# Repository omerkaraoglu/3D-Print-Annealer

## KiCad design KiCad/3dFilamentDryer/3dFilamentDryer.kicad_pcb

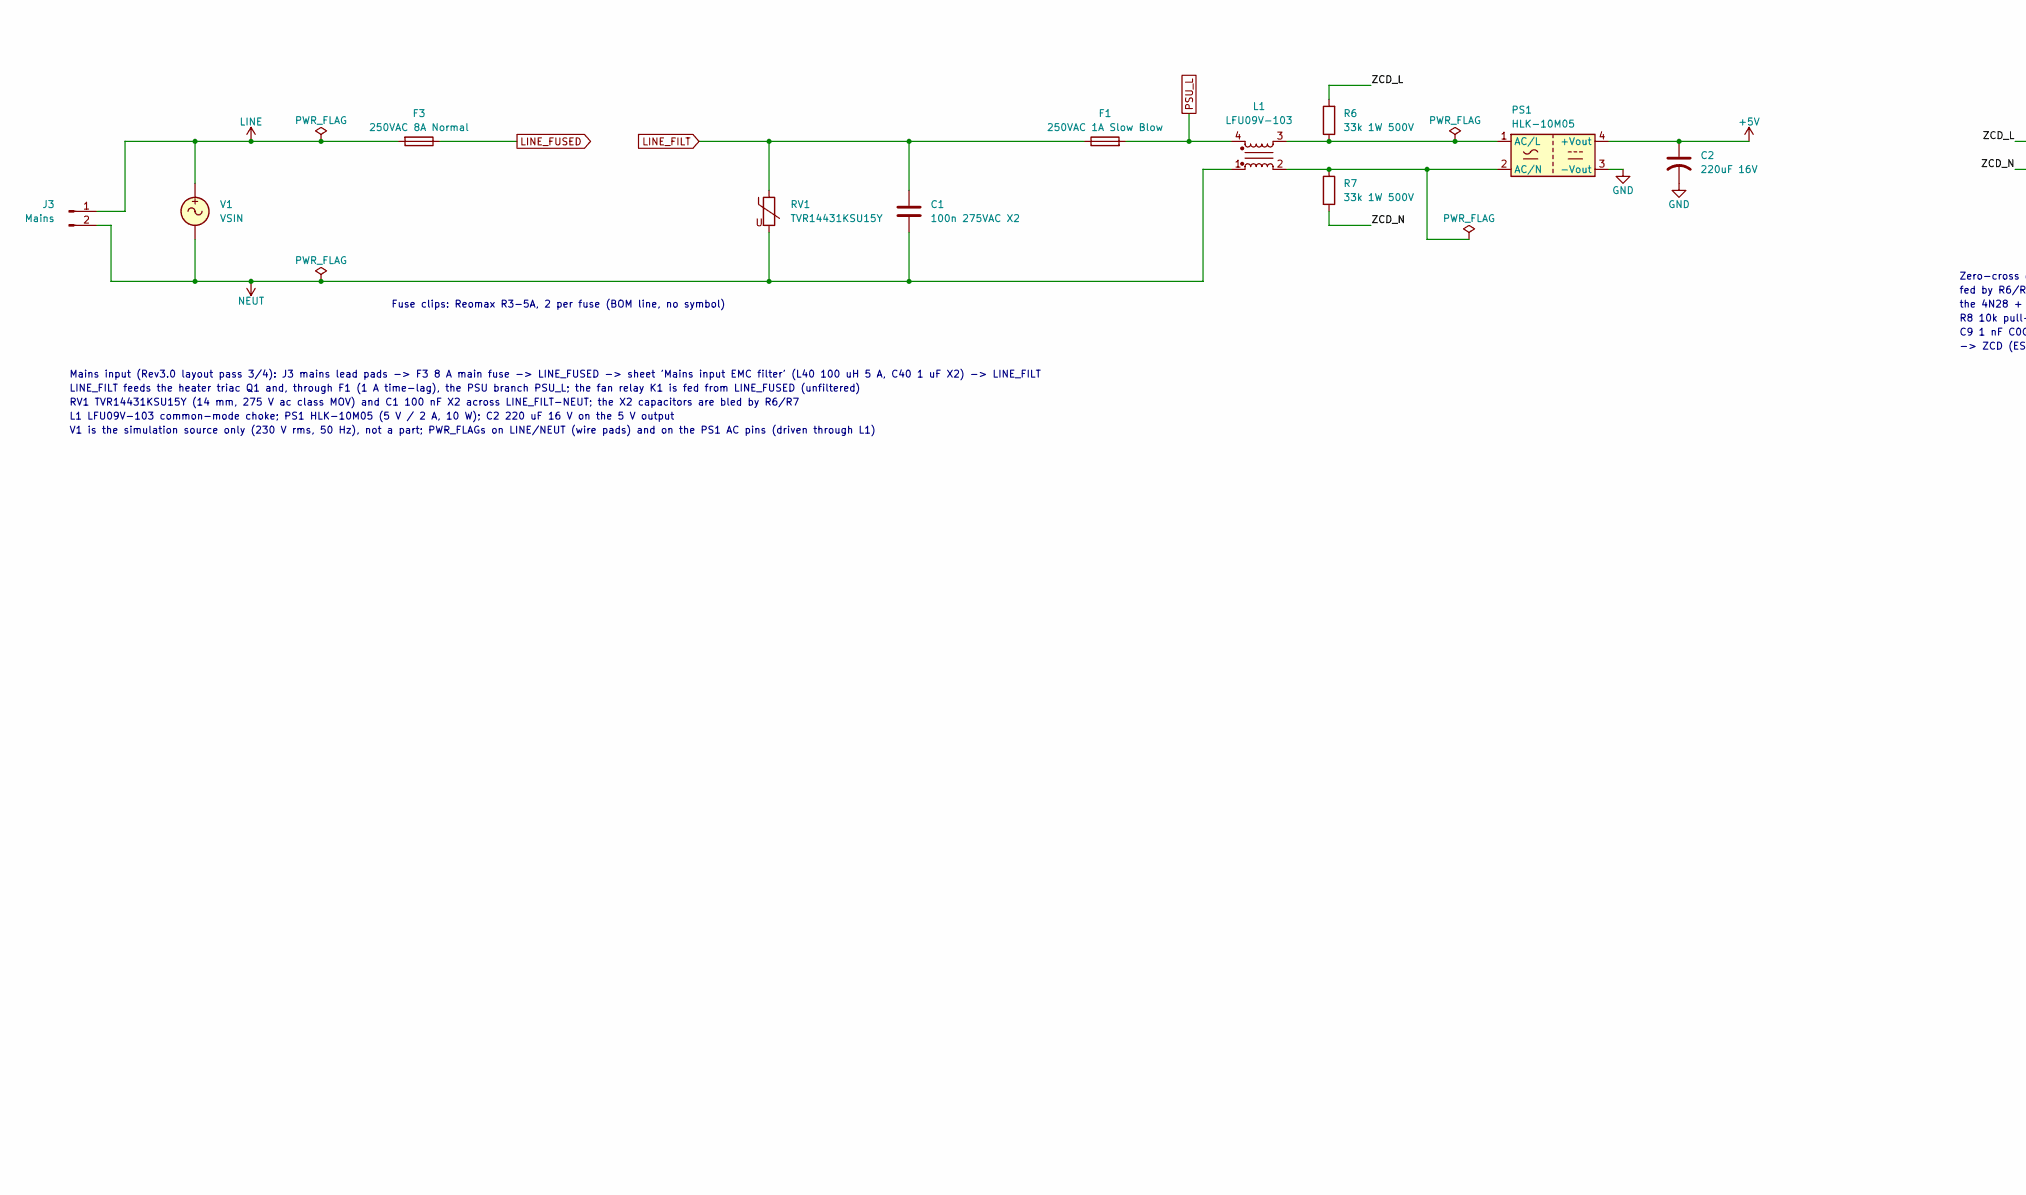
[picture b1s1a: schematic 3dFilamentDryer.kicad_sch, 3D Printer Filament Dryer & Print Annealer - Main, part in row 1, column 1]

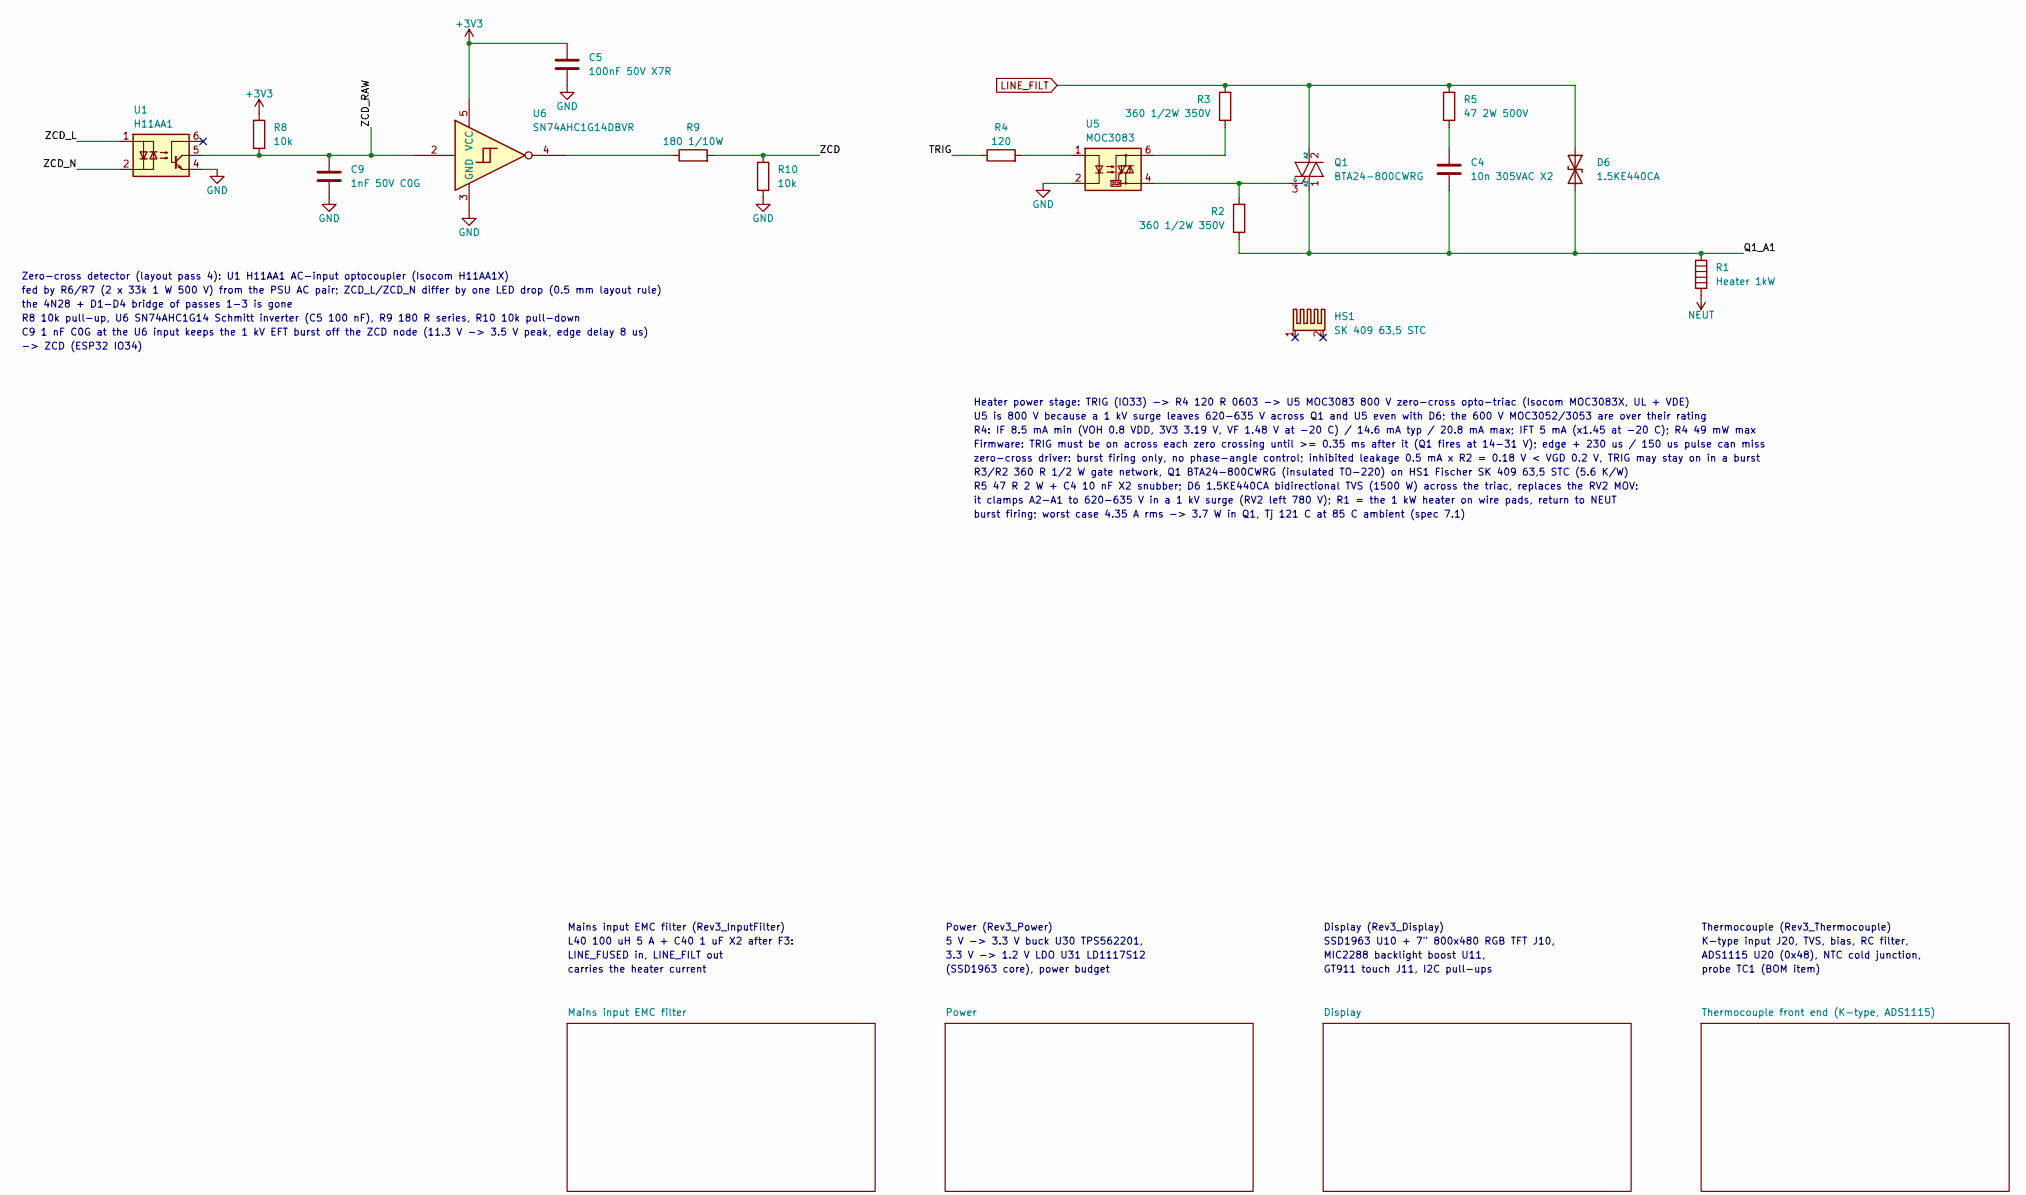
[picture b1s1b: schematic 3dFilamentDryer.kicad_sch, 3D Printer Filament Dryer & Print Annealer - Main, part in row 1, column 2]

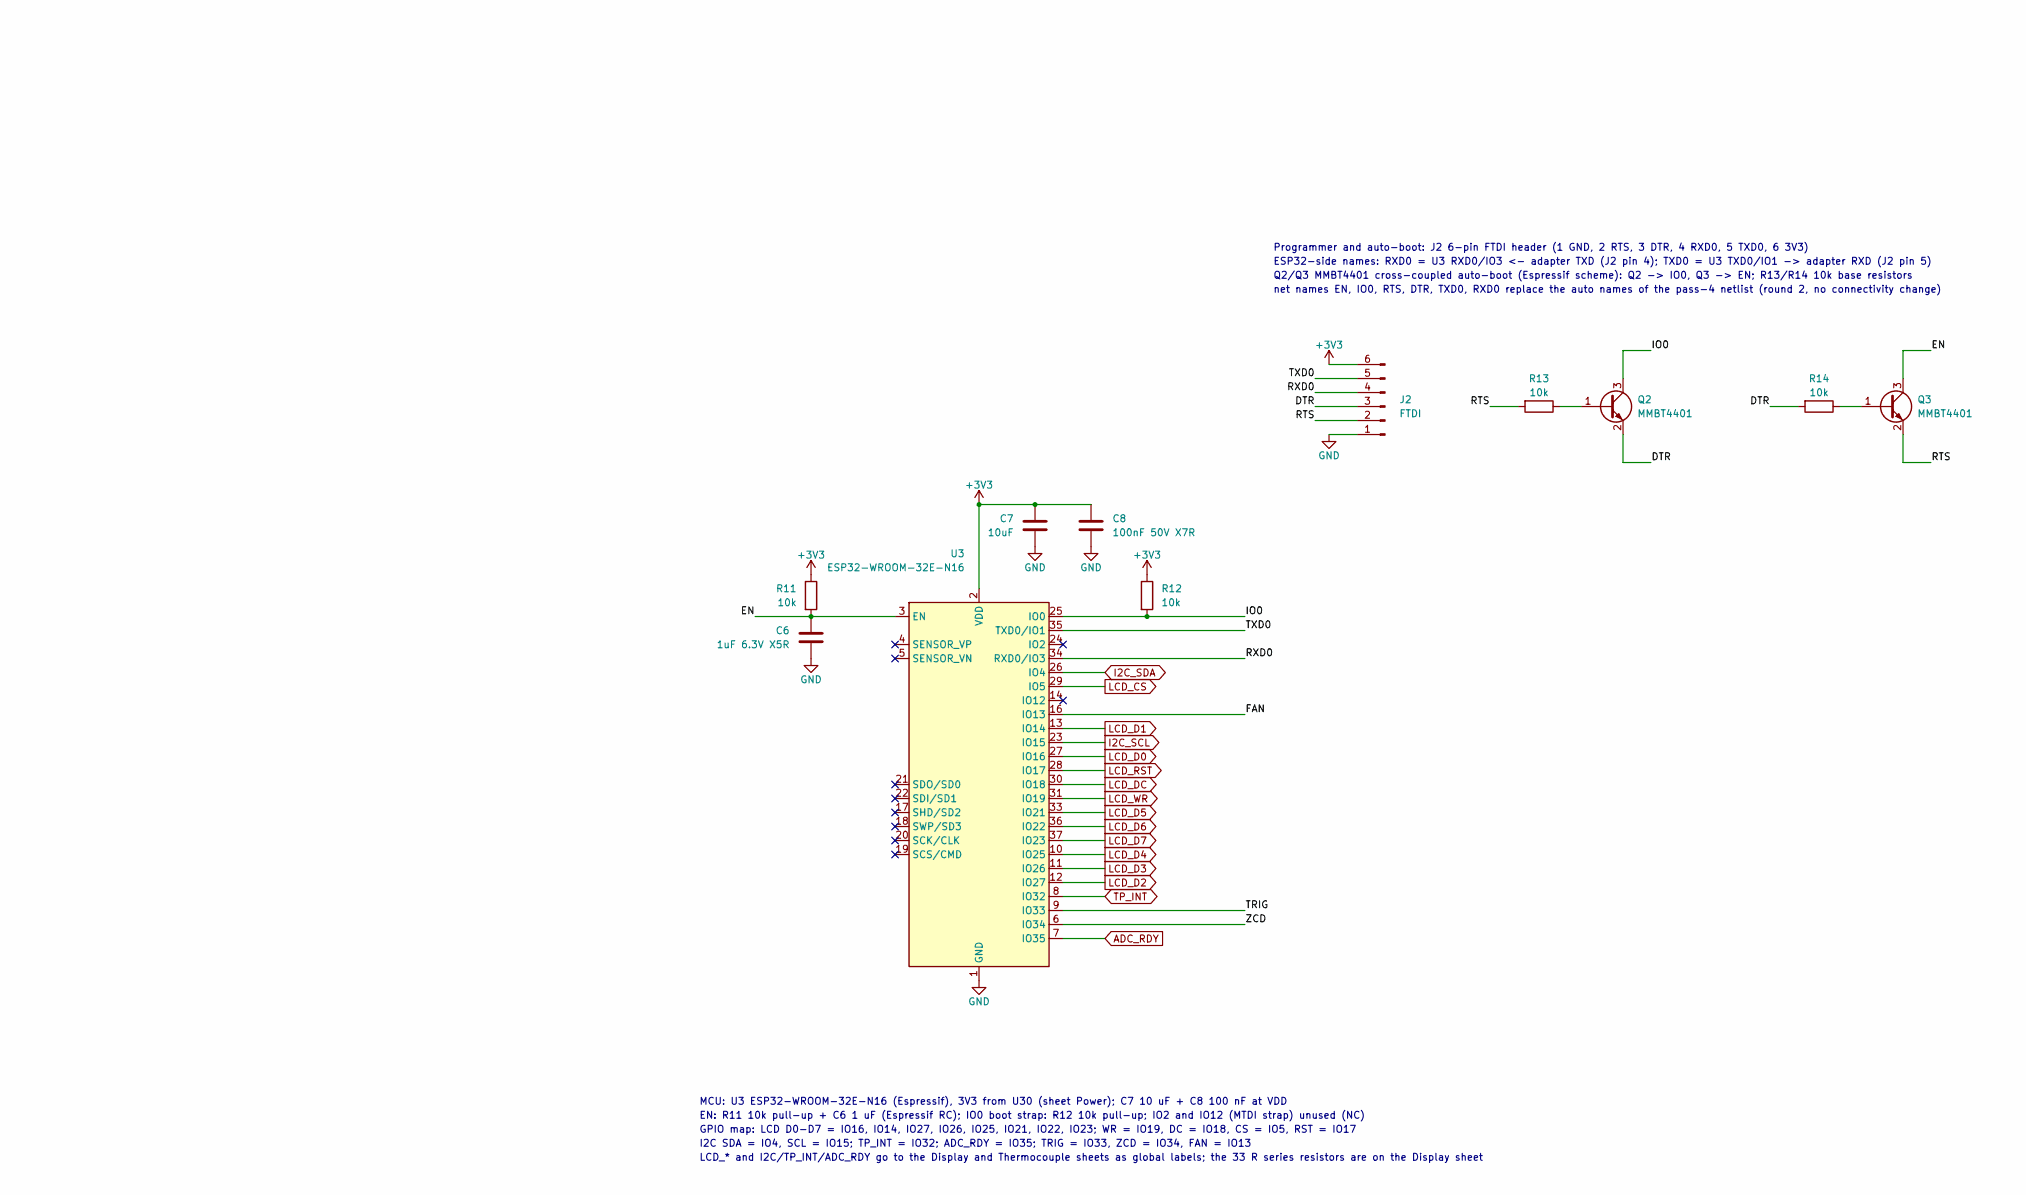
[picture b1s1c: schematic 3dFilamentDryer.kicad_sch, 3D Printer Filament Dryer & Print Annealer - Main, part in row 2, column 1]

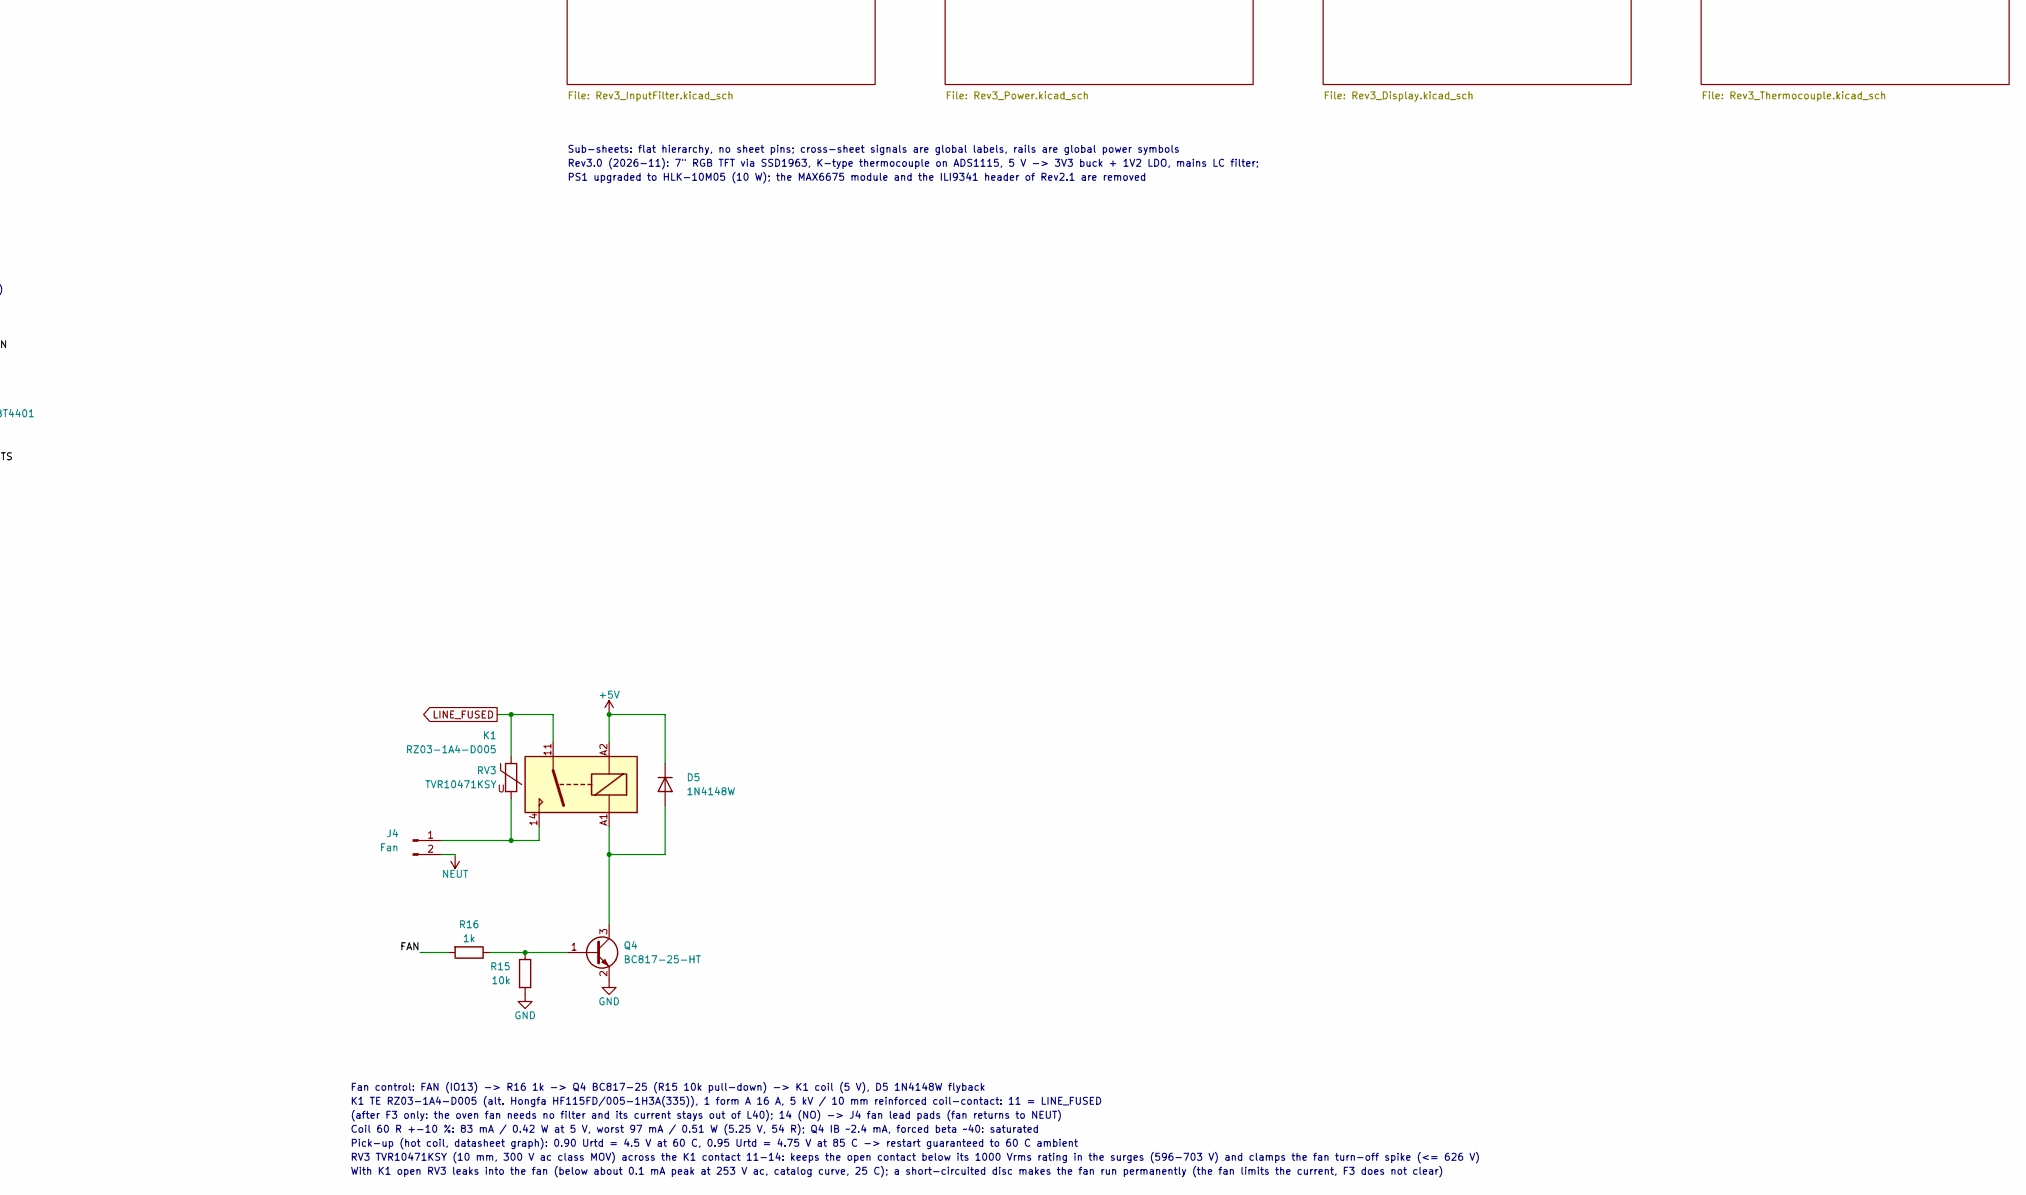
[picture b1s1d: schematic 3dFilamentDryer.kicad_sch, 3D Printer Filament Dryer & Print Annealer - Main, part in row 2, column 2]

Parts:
C1: 100n 275VAC X2; C_Rect_L18.0mm_W5.0mm_P15.00mm_FKS3_FKP3; MPN C42P2104M6SC361
C2: 220uF 16V; C_Radial_D6.3mm_H11.0mm_P2.50mm; MPN PKRJ-016V221ME070-T2.5
C4: 10n 305VAC X2; C_Rect_L13.0mm_W4.0mm_P10.00mm_FKS3_FKP3_MKS4; MPN C42Q2103K40A405
C5, C8: 100nF 50V X7R; C_0402_1005Metric; MPN CC0402KRX7R9BB104
C6: 1uF 6.3V X5R; C_0402_1005Metric; MPN CL05A105KQ5NNNC
C7: 10uF; C_0603_1608Metric; MPN CL10A106KP8NNNC
C9: 1nF 50V C0G; C_0402_1005Metric; MPN CL05C102JB5NNNC
D5: 1N4148W; D_SOD-123; MPN 1N4148W_R1_00301
D6: 1.5KE440CA; D_DO-201AD_P15.24mm_Horizontal; MPN 1.5KE440CA-TKS
F1: 250VAC 1A Slow Blow; Fuseholder_Clip-5x20mm_Littelfuse_445-030_Inline_P20.50x5.2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; MPN STC1A250V
F3: 250VAC 8A Normal; Fuseholder_Clip-5x20mm_Littelfuse_445-030_Inline_P20.50x5.2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; MPN 5GT8A
HS1: SK 409 63,5 STC; Heatsink_Fischer_SK409_63.5_STC; MPN SK 409 63,5 STC TO 220
J2: FTDI; PinHeader_1x06_P2.54mm_Vertical; MPN DS1021-1X6SF11-B
J3: Mains; SolderWire-1.5sqmm_1x02_P7.8mm_D1.7mm_OD3.9mm
J4: Fan; SolderWire-0.75sqmm_1x02_P7mm_D1.25mm_OD3.5mm
K1: RZ03-1A4-D005; Relay_SPST_Schrack-RT1-16A-FormA_RM5mm; MPN RZ03-1A4-D005
L1: LFU09V-103; MPN LFU09V-103
PS1: HLK-10M05; Converter_ACDC_Hi-Link_HLK-10Mxx; MPN HLK-10M05
Q1: BTA24-800CWRG; TO-220-3_Vertical; MPN BTA24-800CWRG
Q2, Q3: MMBT4401; SOT-23-3; MPN MMBT4401-TP
Q4: BC817-25-HT; SOT-23; MPN BC817-25-HT
R1: Heater 1kW; SolderWire-1.5sqmm_1x02_P7.8mm_D1.7mm_OD3.9mm
R2, R3: 360 1/2W 350V; R_Axial_DIN0309_L9.0mm_D3.2mm_P12.70mm_Horizontal; MPN MFR-50FTF52-360R
R4: 120; R_0603_1608Metric; MPN 0603SAJ0121T5E
R5: 47 2W 500V; R_Axial_DIN0414_L11.9mm_D4.5mm_P15.24mm_Horizontal; MPN KNP02SJ0470A10
R6, R7: 33k 1W 500V; R_Axial_DIN0414_L11.9mm_D4.5mm_P5.08mm_Vertical; MPN CFR01SJ0333A10
R8, R10, R11, R12, R13, R14, R15: 10k; R_0402_1005Metric; MPN 0402WGJ0103TCE
R9: 180 1/10W; R_0603_1608Metric; MPN 0603SAJ0181T5E
R16: 1k; R_0402_1005Metric; MPN 0402WGJ0102TCE
RV1: TVR14431KSU15Y; RV_Disc_D15.5mm_W5mm_P7.5mm; MPN TVR14431KSU15Y
RV3: TVR10471KSY; RV_Disc_D12mm_W5.8mm_P7.5mm; MPN TVR10471KSY
U1: H11AA1; DIP-6_W7.62mm; MPN H11AA1X
U3: ESP32-WROOM-32E-N16; ESP32-WROOM-32E; MPN ESP32-WROOM-32E-N16
U5: MOC3083; DIP-6_W7.62mm; MPN MOC3083X
U6: SN74AHC1G14DBVR; SOT-23-5; MPN SN74AHC1G14DBVR
V1: VSIN

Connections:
+3V3: C5.1, C7.1, C8.2, J2.6, R8.1, R11.1, R12.1, U3.2 (VDD), U6.5 (VCC); also elsewhere on the board
+5V: C2.1, D5.1 (K), K1.A2, PS1.4 (+Vout); also elsewhere on the board
/DTR: J2.3, Q2.2 (E), R14.2
/EN: C6.2, Q3.3 (C), R11.2, U3.3 (EN)
/FAN: R16.2, U3.16 (IO13)
/IO0: Q2.3 (C), R12.2, U3.25 (IO0)
/Q1_A1: C4.2, D6.2 (A2), Q1.1 (A1), R1.1, R2.1
/RTS: J2.2, Q3.2 (E), R13.2
/RXD0: J2.4, U3.34 (RXD0/IO3)
/TRIG: R4.1, U3.9 (IO33)
/TXD0: J2.5, U3.35 (TXD0/IO1)
/ZCD: R9.2, R10.1, U3.6 (IO34)
/ZCD_L: R6.2, U1.1
/ZCD_N: R7.2, U1.2
/ZCD_RAW: C9.1, R8.2, U1.5, U6.2
ADC_RDY: U3.7 (IO35); also elsewhere on the board
GND: C2.2, C5.2, C6.1, C7.2, C8.1, C9.2, J2.1, PS1.3 (-Vout), Q4.2 (E), R10.2, R15.2, U1.4, U3.1 (GND), U3.15 (GND), U3.38 (GND), U3.39 (GND), U5.2, U6.3 (GND); also elsewhere on the board
I2C_SCL: U3.23 (IO15); also elsewhere on the board
I2C_SDA: U3.26 (IO4); also elsewhere on the board
LCD_CS: U3.29 (IO5); also elsewhere on the board
LCD_D0: U3.27 (IO16); also elsewhere on the board
LCD_D1: U3.13 (IO14); also elsewhere on the board
LCD_D2: U3.12 (IO27); also elsewhere on the board
LCD_D3: U3.11 (IO26); also elsewhere on the board
LCD_D4: U3.10 (IO25); also elsewhere on the board
LCD_D5: U3.33 (IO21); also elsewhere on the board
LCD_D6: U3.36 (IO22); also elsewhere on the board
LCD_D7: U3.37 (IO23); also elsewhere on the board
LCD_DC: U3.30 (IO18); also elsewhere on the board
LCD_RST: U3.28 (IO17); also elsewhere on the board
LCD_WR: U3.31 (IO19); also elsewhere on the board
LINE: F3.2, J3.1, V1.1
LINE_FILT: C1.1, D6.1 (A1), F1.1, Q1.2 (A2), R3.2, R5.2, RV1.1; also elsewhere on the board
LINE_FUSED: F3.1, K1.11, RV3.1; also elsewhere on the board
NEUT: C1.2, J3.2, J4.2, L1.1, R1.2, RV1.2, V1.2; also elsewhere on the board
unnamed: C4.1, R5.1
unnamed: D5.2 (A), K1.A1, Q4.3 (C)
unnamed: J4.1, K1.14, RV3.2
unnamed: L1.3, PS1.1 (AC/L), R6.1
unnamed: L1.2, PS1.2 (AC/N), R7.1
unnamed: Q1.3 (G), R2.2, U5.4
unnamed: Q2.1 (B), R13.1
unnamed: Q3.1 (B), R14.1
unnamed: Q4.1 (B), R15.1, R16.1
unnamed: R3.1, U5.6
unnamed: R4.2, U5.1
unnamed: R9.1, U6.4
PSU_L: F1.2, L1.4
TP_INT: U3.8 (IO32); also elsewhere on the board

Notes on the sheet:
Fuse clips: Reomax R3-5A, 2 per fuse (BOM line, no symbol)
Mains input (Rev3.0 layout pass 3/4): J3 mains lead pads -> F3 8 A main fuse -> LINE_FUSED -> sheet 'Mains input EMC filter' (L40 100 uH 5 A, C40 1 uF X2) -> LINE_FILT
LINE_FILT feeds the heater triac Q1 and, through F1 (1 A time-lag), the PSU branch PSU_L; the fan relay K1 is fed from LINE_FUSED (unfiltered)
RV1 TVR14431KSU15Y (14 mm, 275 V ac class MOV) and C1 100 nF X2 across LINE_FILT-NEUT; the X2 capacitors are bled by R6/R7
L1 LFU09V-103 common-mode choke; PS1 HLK-10M05 (5 V / 2 A, 10 W); C2 220 uF 16 V on the 5 V output
V1 is the simulation source only (230 V rms, 50 Hz), not a part; PWR_FLAGs on LINE/NEUT (wire pads) and on the PS1 AC pins (driven through L1)
Zero-cross detector (layout pass 4): U1 H11AA1 AC-input optocoupler (Isocom H11AA1X)
fed by R6/R7 (2 x 33k 1 W 500 V) from the PSU AC pair; ZCD_L/ZCD_N differ by one LED drop (0.5 mm layout rule)
the 4N28 + D1-D4 bridge of passes 1-3 is gone
R8 10k pull-up, U6 SN74AHC1G14 Schmitt inverter (C5 100 nF), R9 180 R series, R10 10k pull-down
C9 1 nF C0G at the U6 input keeps the 1 kV EFT burst off the ZCD node (11.3 V -> 3.5 V peak, edge delay 8 us)
-> ZCD (ESP32 IO34)
Heater power stage: TRIG (IO33) -> R4 120 R 0603 -> U5 MOC3083 800 V zero-cross opto-triac (Isocom MOC3083X, UL + VDE)
U5 is 800 V because a 1 kV surge leaves 620-635 V across Q1 and U5 even with D6; the 600 V MOC3052/3053 are over their rating
R4: IF 8.5 mA min (VOH 0.8 VDD, 3V3 3.19 V, VF 1.48 V at -20 C) / 14.6 mA typ / 20.8 mA max; IFT 5 mA (x1.45 at -20 C); R4 49 mW max
Firmware: TRIG must be on across each zero crossing until >= 0.35 ms after it (Q1 fires at 14-31 V); edge + 230 us / 150 us pulse can miss
zero-cross driver: burst firing only, no phase-angle control; inhibited leakage 0.5 mA x R2 = 0.18 V < VGD 0.2 V, TRIG may stay on in a burst
R3/R2 360 R 1/2 W gate network, Q1 BTA24-800CWRG (insulated TO-220) on HS1 Fischer SK 409 63,5 STC (5.6 K/W)
R5 47 R 2 W + C4 10 nF X2 snubber; D6 1.5KE440CA bidirectional TVS (1500 W) across the triac, replaces the RV2 MOV:
it clamps A2-A1 to 620-635 V in a 1 kV surge (RV2 left 780 V); R1 = the 1 kW heater on wire pads, return to NEUT
burst firing; worst case 4.35 A rms -> 3.7 W in Q1, Tj 121 C at 85 C ambient (spec 7.1)
Mains input EMC filter (Rev3_InputFilter)
L40 100 uH 5 A + C40 1 uF X2 after F3:
LINE_FUSED in, LINE_FILT out
carries the heater current
Power (Rev3_Power)
5 V -> 3.3 V buck U30 TPS562201,
3.3 V -> 1.2 V LDO U31 LD1117S12
(SSD1963 core), power budget
Display (Rev3_Display)
SSD1963 U10 + 7" 800x480 RGB TFT J10,
MIC2288 backlight boost U11,
GT911 touch J11, I2C pull-ups
Thermocouple (Rev3_Thermocouple)
K-type input J20, TVS, bias, RC filter,
ADS1115 U20 (0x48), NTC cold junction,
probe TC1 (BOM item)
Sub-sheets: flat hierarchy, no sheet pins; cross-sheet signals are global labels, rails are global power symbols
Rev3.0 (2026-11): 7" RGB TFT via SSD1963, K-type thermocouple on ADS1115, 5 V -> 3V3 buck + 1V2 LDO, mains LC filter;
PS1 upgraded to HLK-10M05 (10 W); the MAX6675 module and the ILI9341 header of Rev2.1 are removed

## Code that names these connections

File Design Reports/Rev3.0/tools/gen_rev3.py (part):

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# Custom library symbols
# ----------------------------------------------------------------------------------
def lib_pin(ptype, x, y, angle, length, name, number, hide=False):
    p = [S('pin'), S(ptype), S('line'), [S('at'), num(x), num(y), num(angle)], [S('length'), num(length)]]
    if hide:
        p.append([S('hide'), S('yes')])
    p.append([S('name'), name, effects()])
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    sh.net(u, '3', '+5V', 'power', 5.08)          # VIN
    sh.net(u, '5', '+5V', 'power', 5.08)          # EN tied to VIN (EN abs max 6.5 V)
    sh.net(u, '1', 'GND', 'power', 2.54)          # GND
    sh.net(u, '2', 'BUCK_SW', 'label', 5.08)      # SW
    sh.net(u, '6', 'BUCK_BST', 'label', 5.08)     # VBST
    sh.net(u, '4', 'BUCK_FB', 'label', 5.08)      # VFB
    two_pin(sh, ('Device', 'C'), 'C330', 50, 70, '10uF 10V X5R', C0805, '+5V', 'GND', topkind='power', botkind='power')
    two_pin(sh, ('Device', 'C'), 'C331', 60, 70, '10uF 10V X5R', C0805, '+5V', 'GND', topkind='power', botkind='power')
    two_pin(sh, ('Device', 'C'), 'C332', 120, 60, '100nF 25V X7R', C0402, 'BUCK_BST', 'BUCK_SW')
    two_pin(sh, ('Device', 'L'), 'L30', 135, 70, '4.7uH 4A', 'Inductor_SMD:L_Bourns_SRN6045TA', 'BUCK_SW', '+3V3',
            botkind='power', fields={'MPN': 'SRI0605B-4R7M', 'Manufacturer': 'Core Master', 'Datasheet': URLS['SRI0605B-4R7M'],
                                     'Description': 'Shielded power inductor 4.7 uH 4 A 70 mOhm 6.6x6.2x5 mm (footprint placeholder: verify against SRI0605B drawing)'})
    two_pin(sh, ('Device', 'R'), 'R330', 150, 62, '33.2k 1%', R0402, '+3V3', 'BUCK_FB', topkind='power')
    two_pin(sh, ('Device', 'R'), 'R331', 150, 78, '10k 1%', R0402, 'BUCK_FB', 'GND', botkind='power')
    two_pin(sh, ('Device', 'C'), 'C333', 165, 70, '22uF 10V X5R', C0805, '+3V3', 'GND', topkind='power', botkind='power')
    two_pin(sh, ('Device', 'C'), 'C334', 175, 70, '22uF 10V X5R', C0805, '+3V3', 'GND', topkind='power', botkind='power')
    # LDO
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             footprint='TerminalBlock_Phoenix:TerminalBlock_Phoenix_MKDS-1,5-2-5.08_1x02_P5.08mm_Horizontal',
             fields={'MPN': 'DG127H-5.08-02P-14-00AH', 'Manufacturer': 'DEGSON', 'Datasheet': URLS['DG127H-5.08-02P-14-00AH'],
                     'Description': 'PCB screw terminal block 2-pin 5.08 mm, 12 A 300 V, 26-14 AWG'})
    sh.net('J20', '1', 'TC_P', 'label', 5.08)
    sh.net('J20', '2', 'TC_N', 'label', 5.08)
    for ref, net, x in (('D220', 'TC_P', 60), ('D221', 'TC_N', 70)):
        sh.place(('Device', 'D_TVS'), ref, x, 100, 90, value='PESD5V0S1BA', footprint='Diode_SMD:D_SOD-323',
                 fields={'MPN': 'PESD5V0S1BA,115', 'Manufacturer': 'Nexperia', 'Datasheet': URLS['PESD5V0S1BA'],
                         'Description': 'Bidirectional ESD/TVS diode 5 V 130 W SOD-323'})
        sh.net(ref, '1', net, 'label', 2.54)
        sh.net(ref, '2', 'GND', 'power', 2.54)
    two_pin(sh, ('Device', 'R'), 'R220', 85, 72, '1k 0.1%', R0603, 'TC_P', 'TCF_P', rot=90)
    two_pin(sh, ('Device', 'R'), 'R221', 85, 88, '1k 0.1%', R0603, 'TC_N', 'TCF_N', rot=90)
    two_pin(sh, ('Device', 'C'), 'C220', 100, 80, '100nF 50V X7R', C0603, 'TCF_P', 'TCF_N')
    two_pin(sh, ('Device', 'C'), 'C221', 110, 65, '10nF 50V C0G 1%', C0603, 'TCF_P', 'GND', botkind='power')
    two_pin(sh, ('Device', 'C'), 'C222', 110, 95, '10nF 50V C0G 1%', C0603, 'TCF_N', 'GND', botkind='power')
    two_pin(sh, ('Device', 'R'), 'R222', 70, 60, '10M', R0603, '+3V3', 'TC_P', topkind='power')
    two_pin(sh, ('Device', 'R'), 'R223', 70, 100, '10M', R0603, 'TC_N', 'GND', botkind='power')
    # ADC
    u = 'U20'
    sh.place(('Analog_ADC', 'ADS1115IDGS'), u, 160, 80, 0, value='ADS1115IDGSR',
             fields={'MPN': 'ADS1115IDGSR', 'Manufacturer': 'Texas Instruments', 'Datasheet': URLS['ADS1115IDGSR'],
                     'Description': '16-bit delta-sigma ADC, 4 ch, PGA, I2C, 860 SPS, VSSOP-10, -40..+125 C'})
    sh.net(u, '4', 'TCF_P', 'label', 5.08)
    sh.net(u, '5', 'TCF_N', 'label', 5.08)
    sh.net(u, '6', 'NTC_MID', 'label', 5.08)
    sh.net(u, '7', 'VREF_HALF', 'label', 5.08)
    sh.net(u, '8', '+3V3', 'power', 2.54)
    sh.net(u, '3', 'GND', 'power', 2.54)
    sh.net(u, '1', 'GND', 'power', 5.08)        # ADDR -> 0x48
    sh.net(u, '2', 'ADC_RDY', 'global', 7.62, shape='output')
    sh.net(u, '9', 'I2C_SDA', 'global', 7.62)
    sh.net(u, '10', 'I2C_SCL', 'global', 7.62, shape='input')
    two_pin(sh, ('Device', 'R'), 'R224', 190, 62, '10k', R0402, '+3V3', 'ADC_RDY', topkind='power', botkind='global')
    two_pin(sh, ('Device', 'C'), 'C223', 140, 55, '100nF 16V X7R', C0402, '+3V3', 'GND', topkind='power', botkind='power')
    two_pin(sh, ('Device', 'C'), 'C224', 150, 55, '1uF 16V X7R', C0603, '+3V3', 'GND', topkind='power', botkind='power')
    # CJC NTC + reference
    two_pin(sh, ('Device', 'Thermistor_NTC'), 'TH220', 60, 130, '10k NTC B3380', R0603, '+3V3', 'NTC_MID', topkind='power',
            fields={'MPN': 'NCP18XH103F03RB', 'Manufacturer': 'Murata', 'Datasheet': URLS['NCP18XH103F03RB'],
                    'Description': 'NTC thermistor 10k 1% B25/50=3380K 0603 - cold junction sensor, place touching J20'})
    two_pin(sh, ('Device', 'R'), 'R225', 60, 150, '10k 0.1%', R0603, 'NTC_MID', 'GND', botkind='power')
    two_pin(sh, ('Device', 'C'), 'C225', 75, 150, '100nF 16V X7R', C0402, 'NTC_MID', 'GND', botkind='power')
    two_pin(sh, ('Device', 'R'), 'R226', 100, 130, '10k 0.1%', R0603, '+3V3', 'VREF_HALF', topkind='power')
    two_pin(sh, ('Device', 'R'), 'R227', 100, 150, '10k 0.1%', R0603, 'VREF_HALF', 'GND', botkind='power')
    two_pin(sh, ('Device', 'C'), 'C226', 115, 150, '100nF 16V X7R', C0402, 'VREF_HALF', 'GND', botkind='power')
    return sh

# ----------------------------------------------------------------------------------
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        sh.net(u, str(dmap[i]), f'SSD_D{i}', 'label', 5.08)
    for n in (113, 112, 111, 107, 106, 105, 104, 103, 99, 98, 88, 87, 92, 91, 90, 89):   # D8..D23
        sh.no_connect(u, str(n))
    sh.net(u, '123', 'SSD_CS', 'label', 5.08)
    sh.net(u, '122', 'SSD_DC', 'label', 5.08)
    sh.net(u, '120', 'SSD_WR', 'label', 5.08)
    sh.net(u, '121', 'SSD_RD', 'label', 5.08)
    sh.net(u, '127', 'SSD_RST', 'label', 5.08)
    sh.net(u, '128', '+3V3', 'power', 5.08)       # CONF = 1 -> 8080
    sh.no_connect(u, '50')                        # TE
    sh.net(u, '15', 'GND', 'power', 5.08)         # CLK unused -> VSS
    sh.net(u, '22', 'XTAL_IN', 'label', 5.08)
    sh.net(u, '24', 'XTAL_OUT', 'label', 5.08)
    # LCD side
    lmap = {23: 28, 22: 29, 21: 30, 20: 31, 17: 35, 16: 59, 15: 60, 14: 61, 13: 62, 12: 63, 11: 67, 10: 68, 9: 69,
            8: 70, 7: 71, 6: 72, 5: 76, 4: 77, 3: 78, 2: 79, 1: 80, 0: 81, 19: 85, 18: 86}
    for i in range(24):
        col = 'RGB'[2 - i // 8]       # LDATA0-7 = B, 8-15 = G, 16-23 = R
        sh.net(u, str(lmap[i]), f'{col}{i % 8}', 'label', 5.08)
    sh.net(u, '45', 'PCLK', 'label', 5.08)
    sh.net(u, '44', 'HSYNC', 'label', 5.08)
    sh.net(u, '43', 'VSYNC', 'label', 5.08)
    sh.net(u, '49', 'DE', 'label', 5.08)
    sh.net(u, '51', 'BL_PWM', 'label', 5.08)
    for n in ('36', '37', '38', '39', '52', '53'):
        sh.no_connect(u, n)
    # power pins (stacked: connect visible ones)
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        x = 60 + (k % 6) * 15
        y = 70 + (k // 6) * 30
        two_pin(sh, ('Device', 'R'), ref, x, y, '33R', R0402, g, l, topkind='global', stub=3.81)
    two_pin(sh, ('Device', 'R'), 'R124', 150, 70, '10k', R0402, '+3V3', 'SSD_RD', topkind='power')
    # crystal
    sh.place(('Device', 'Crystal_GND24'), 'Y10', 100, 130, 0, value='10MHz', footprint='Crystal:Crystal_SMD_3225-4Pin_3.2x2.5mm',
             fields={'MPN': 'CX3225GB10000P0HPQCC', 'Manufacturer': 'Kyocera AVX', 'Datasheet': URLS['CX3225GB10000P0HPQCC'],
                     'Description': 'Crystal 10 MHz 18 pF 3225 4-pad, +/-20 ppm'})
    sh.net('Y10', '1', 'XTAL_IN', 'label', 3.81)
    sh.net('Y10', '3', 'XTAL_OUT', 'label', 3.81)
    sh.net('Y10', '2', 'GND', 'power', 2.54)
    two_pin(sh, ('Device', 'C'), 'C110', 85, 145, '27pF C0G', C0402, 'XTAL_IN', 'GND', botkind='power')
    two_pin(sh, ('Device', 'C'), 'C111', 115, 145, '27pF C0G', C0402, 'XTAL_OUT', 'GND', botkind='power')
    # decoupling
    x = 60
    for ref, val, fp, net in (('C112', '100nF 16V X7R', C0402, '+3V3'), ('C113', '100nF 16V X7R', C0402, '+3V3'),
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        sh.net(j, str(5 + i), f'R{i}', 'label', 5.08)
        sh.net(j, str(13 + i), f'G{i}', 'label', 5.08)
        sh.net(j, str(21 + i), f'B{i}', 'label', 5.08)
    sh.net(j, '30', 'PCLK', 'label', 5.08)
    sh.net(j, '32', 'HSYNC', 'label', 5.08)
    sh.net(j, '33', 'VSYNC', 'label', 5.08)
    sh.net(j, '34', 'DE', 'label', 5.08)
    sh.net(j, '1', 'VLED_N', 'label', 5.08)
    sh.net(j, '2', 'VLED_P', 'label', 5.08)
    sh.net(j, '4', 'TFT_VDD', 'label', 5.08)
    for n in ('3', '29', '36'):
        sh.net(j, n, 'GND', 'power', 5.08)
    for n in ('31', '35', '37', '38', '39', '40'):
        sh.no_connect(j, n)
    # panel supply: ferrite bead-less, just caps (10uF + 100nF) + 0R link from 3V3 so the panel can be isolated for debugging
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
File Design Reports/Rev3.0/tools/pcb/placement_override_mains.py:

# Mains region, layout pass 4 (mains agent).  Executed by placement.py after its own list; put(ref, x, y, rot[, side]).
# Pass 4: PS1 sits in the top-right corner, so the PSU/ZCD block that lived at x 130..163 moves next to it, the triac goes on the
# heatsink's NORTH face (Q1 rot 180), the input filter (F3 -> L40 -> C40/C1/RV1) moves to the west end and the H11AA1 replaces
# the 4N28 + D1..D4 bridge (R6/R7 feed U1.1/U1.2 directly).  Heater loop: J3.L -> F3 -> L40 -> LINE_FILT trunk (F.Cu, y 12.8,
# then straight down x 103.0 into Q1.2) / Q1.1 -> A1 trunk (F.Cu, straight down x 108.0 from R1.1) / R1.N -> J3.N on the top edge.
# Triac drive parts are "rungs" across the two vertical trunks (or hang off the LINE_FILT trunk to the west); everything east of
# the A1 trunk is the PSU/ZCD block: L1 top right at PS1's AC pins, R7/R6 under it, F1 straddling the A1 trunk.
#
# top edge (wire pads and the main fuse), west to east
put('J4', 49.9, 3.5, 0)       # fan wire pads: NO 49.9 (B.Cu down the west side to K1 NO), N 56.9 (2.6 mm from the LINE_FUSED clip link)
put('F3', 62.4, 3.5, 0)       # main fuse: LINE_FUSED clips 62.4/67.6 (67.6 drops straight into L40.2), LINE clips 72.7/77.9 next to J3.L
put('J3', 87.0, 3.5, 0)       # mains wire pads: L 87.0 (9.1 mm to F3.2b), N 94.8 (5.4 mm to R1.N)
put('R1', 108.0, 3.5, 180)    # heater wire pads: N 100.2 (heater return to J3.N on the top edge), A1 108.0 = top of the A1 trunk
# west end: input filter (approved option 2)
put('L40', 72.3, 15.1, 180)   # RC1415U: LINE_FUSED 68.55 under F3.1b, LINE_FILT 76.05 -> trunk; x >= 72.25 keeps its round courtyard off C40
put('C40', 47.0, 13.0, 180)   # 1 uF X2 west of L40: LINE_FILT 60.75 (y 18 bus from L40.1), NEUT 33.25 (>= 6.4 mm from the LV edge x 25.5)
put('C1', 48.2, 21.4, 180)    # 100 nF X2 under C40: LINE_FILT 48.2, NEUT 33.2 (6.5 mm creepage to x 25.5)
put('RV1', 44.0, 28.0, 180)   # 14 mm MOV under C1: LINE_FILT 44.0 / NEUT 36.5; pads >= 6.4 mm from the LV edge y 35.5
# heatsink + triac (decision 1): HS1.x 103.0 so that (a) F1's PSU_L clip clears R7's AC/N pad by 2.5 mm east of the A1 trunk
# and (b) the /ZCD_L line to U1.1 still passes heatsink pin 2 at >= 2.5 mm (needs HS1.x >= 102.9)
put('HS1', 103.0, 39.3, 0)    # envelope x 80.5..125.5 (2.6 mm from K1, 5.1 mm from PS1); pins (85.25, 39.3) / (120.75, 39.3)
put('Q1', 105.54, 34.6, 180)  # north face, rot 180 at (HS1.x + 2.54, HS1.y - 4.7): G 100.46, LINE_FILT 103.0, A1 105.54
# triac drive: west-hanging parts on the LINE_FILT trunk (y 12.8) and rungs across the two vertical trunks
put('R3', 84.5, 25.5, 90)     # 360R MOC feed: LINE_FILT pad on the trunk (84.5, 12.8), R3-P1 pad 25.5 -> B.Cu under the heatsink to U5.6
put('R5', 89.0, 28.04, 90)    # snubber R: LINE_FILT pad on the trunk (89.0, 12.8), C4-node pad 28.04 -> C4.1
put('RV2', 100.5, 12.5, 0)    # triac MOV rung: LINE_FILT 100.5 at the trunk corner, A1 on the A1 trunk (108.0, 13.9)
put('F1', 97.6, 20.4, 0)      # PSU fuse rung: LINE_FILT clips 97.6/102.8 (on the descent), PSU_L clips 112.9/118.1 east of the A1 trunk
put('C4', 98.25, 25.5, 0)     # snubber C rung: C4-node 98.25 (2.5 mm from the descent), A1 108.25 on the A1 trunk
put('R2', 110.6, 29.8, 180)   # gate-A1 resistor rung: G 97.9 (-> Q1.3), A1 110.6 (stub to the trunk)
# PSU / ZCD block between the A1 trunk and PS1
put('L1', 123.5, 9.0, 0)      # CM choke at PS1's AC pins: PSU_L (120,5) / NEUT (120,13) west, AC/L (127,5) / AC/N (127,13) east
put('R7', 123.0, 20.0, 270)   # 33k AC/N tap under L1.2: AC/N 20.0 on top, /ZCD_N 25.08 below -> U1.2 on B.Cu
put('R6', 128.0, 20.0, 270)   # 33k AC/L tap (fed on B.Cu under PS1's west edge): AC/L 20.0, /ZCD_L 25.08 -> U1.1 on B.Cu
